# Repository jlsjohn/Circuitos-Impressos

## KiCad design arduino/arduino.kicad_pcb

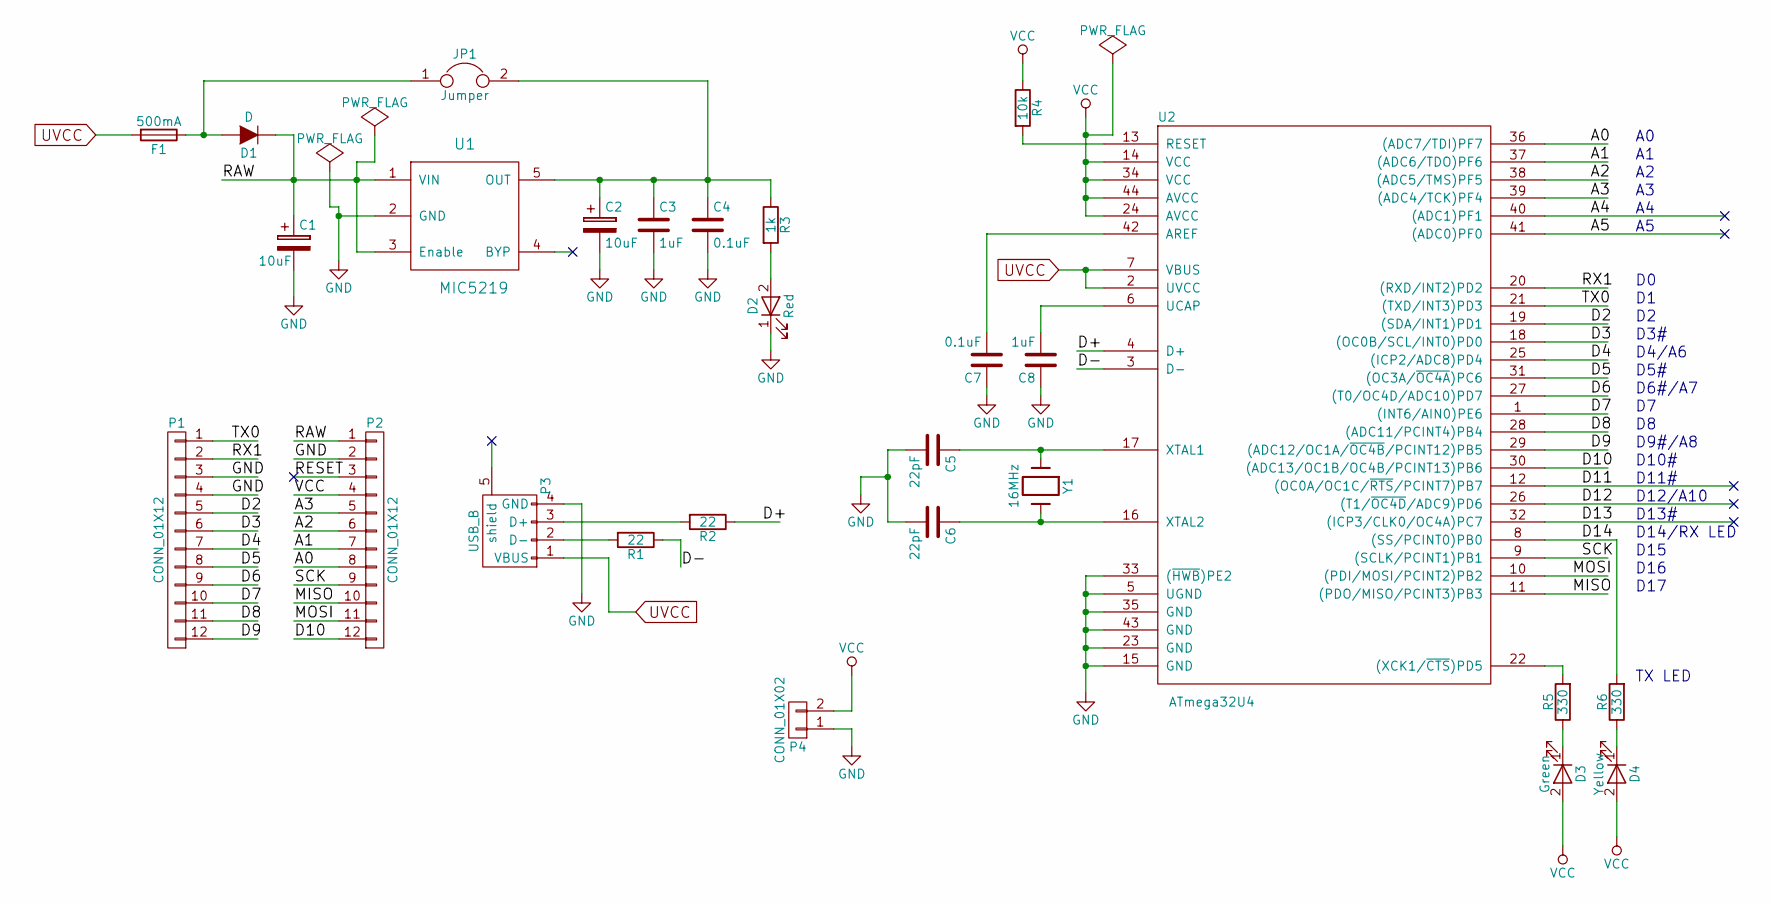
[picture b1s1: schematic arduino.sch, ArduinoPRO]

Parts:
C1, C2: 10uF; CP_Elec_3x5.3
C3, C8: 1uF; C_0805
C4, C7: 0.1uF; C_0805
C5, C6: 22pF; C_0805
D1: D; D_0805
D2: Red; LED_0805
D3: Green; LED_0805
D4: Yellow; LED_0805
F1: 500mA; Fuse_SMD
JP1: Jumper; WireConnection_0.80mmDrill
P1, P2: CONN_01X12; JST_EH_B12B-EH-A_12x2.50mm_Straight
P3: USB_B
P4: CONN_01X02; Connector_Microfit3_Header_02x01_Straight_43045-0228
R1, R2: 22; R_0805
R3: 1k; R_0805
R4: 10k; R_0805
R5, R6: 330; R_0805
U1: MIC5219; SOT-23-5
U2: ATmega32U4; PLCC-44
Y1: 16MHz; Crystal_SMD_5032-2pin_5.0x3.2mm

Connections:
/A0: P2.8, U2.36 ((ADC7/TDI)PF7)
/A1: P2.7, U2.37 ((ADC6/TDO)PF6)
/A2: P2.6, U2.38 ((ADC5/TMS)PF5)
/A3: P2.5, U2.39 ((ADC4/TCK)PF4)
/A4: U2.40 ((ADC1)PF1)
/A5: U2.41 ((ADC0)PF0)
/D2: P1.5, U2.19 ((SDA/INT1)PD1)
/D3: P1.6, U2.18 ((OC0B/SCL/INT0)PD0)
/D4: P1.7, U2.25 ((ICP2/ADC8)PD4)
/D5: P1.8, U2.31 ((OC3A/~OC4A~)PC6)
/D6: P1.9, U2.27 ((T0/OC4D/ADC10)PD7)
/D7: P1.10, U2.1 ((INT6/AIN0)PE6)
/D8: P1.11, U2.28 ((ADC11/PCINT4)PB4)
/D9: P1.12, U2.29 ((ADC12/OC1A/~OC4B~/PCINT12)PB5)
/D10: P2.12, U2.30 ((ADC13/OC1B/OC4B/PCINT13)PB6)
/D11: U2.12 ((OC0A/OC1C/~RTS~/PCINT7)PB7)
/D12: U2.26 ((T1/~OC4D~/ADC9)PD6)
/D13: U2.32 ((ICP3/CLK0/OC4A)PC7)
/D14: R6.2, U2.8 ((SS/PCINT0)PB0)
/D+: R2.1, U2.4 (D+)
/D-: R1.1, U2.3 (D-)
/MISO: P2.10, U2.11 ((PDO/MISO/PCINT3)PB3)
/MOSI: P2.11, U2.10 ((PDI/MOSI/PCINT2)PB2)
/RAW: C1.1, D1.1 (K), P2.1, U1.1 (VIN), U1.3 (Enable)
/RESET: P2.3
/RX1: P1.2, U2.20 ((RXD/INT2)PD2)
/SCK: P2.9, U2.9 ((SCLK/PCINT1)PB1)
/TX0: P1.1, U2.21 ((TXD/INT3)PD3)
GND: C1.2, C2.2, C3.2, C4.2, C5.2, C6.2, C7.1, C8.1, D2.1 (K), P1.3, P1.4, P2.2, P3.4 (GND), P4.1, U1.2 (GND), U2.5 (UGND), U2.15 (GND), U2.23 (GND), U2.33 ((~HWB~)PE2), U2.35 (GND), U2.43 (GND)
unnamed: C2.1, C3.1, C4.1, JP1.2, R3.1, U1.5 (OUT)
unnamed: C5.1, U2.17 (XTAL1), Y1.1
unnamed: C6.1, U2.16 (XTAL2), Y1.2
unnamed: C7.2, U2.42 (AREF)
unnamed: C8.2, U2.6 (UCAP)
unnamed: D1.2 (A), F1.1, JP1.1
unnamed: D2.2 (A), R3.2
unnamed: D3.1 (K), R5.1
unnamed: D4.1 (K), R6.1
unnamed: P3.2 (D-), R1.2
unnamed: P3.3 (D+), R2.2
unnamed: R4.2, U2.13 (RESET)
unnamed: R5.2, U2.22 ((XCK1/~CTS~)PD5)
UVCC: F1.2, P3.1 (VBUS), U2.2 (UVCC), U2.7 (VBUS)
VCC: D3.2 (A), D4.2 (A), P2.4, P4.2, R4.1, U2.14 (VCC), U2.24 (AVCC), U2.34 (VCC), U2.44 (AVCC)

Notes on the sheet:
D3#
D4/A6
D5#
D6#/A7
D9#/A8
D10#
D11#
D12/A10
D13#
D14/RX LED
D15
D16
D17
TX LED

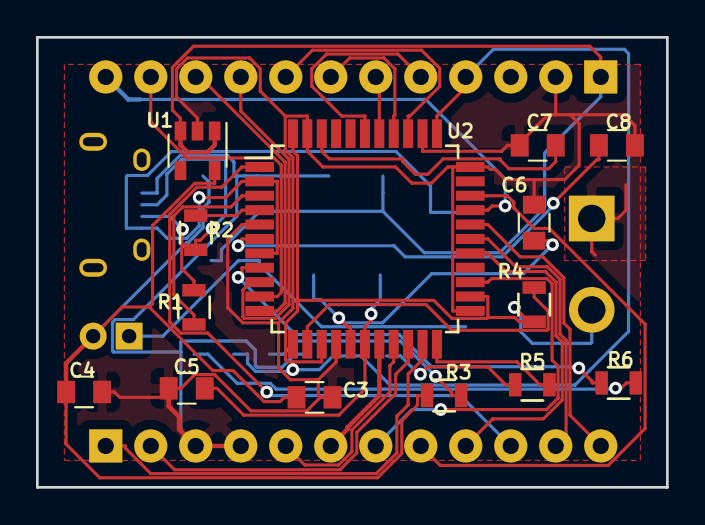
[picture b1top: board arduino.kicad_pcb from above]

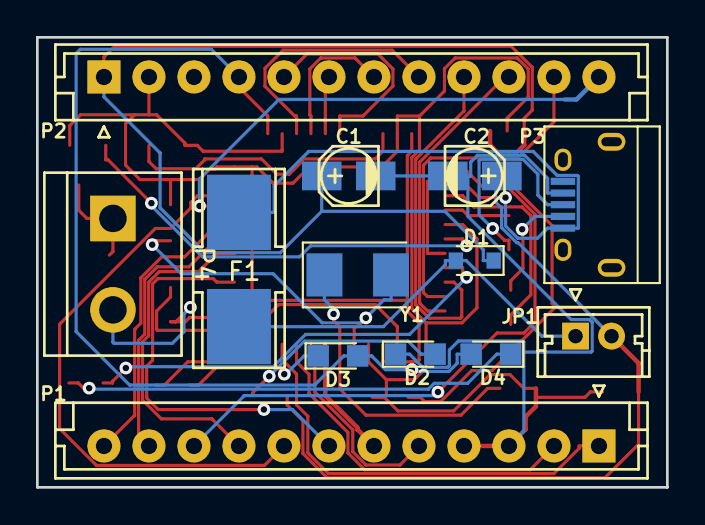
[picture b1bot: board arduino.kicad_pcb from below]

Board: 2 copper layers, 35.0 x 25.0 mm, 27 parts (13 on the bottom side), 38 nets.

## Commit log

2017-02-19 Atividades Concluidas
